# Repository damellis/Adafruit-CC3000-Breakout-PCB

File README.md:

Derivative of the Adafruit CC3000 Breakout PCB
==============================================
This is a derivative of the PCB for the Adafruit CC3000 WiFi Breakout. It adds an ATmega1284 and associated circuitry.

# Original Text Follows

This is the PCB for the Adafruit CC3000 WiFi Breakout
Format is EagleCAD schematic and board layout

For more details, check out the product page at

-----> http://www.adafruit.com/products/1510
-----> http://www.adafruit.com/products/1469

Adafruit invests time and resources providing this open source design, 
please support Adafruit and open-source hardware by purchasing 
products from Adafruit!

Designed by Adafruit Industries.  
Creative Commons Attribution, Share-Alike license, check license.txt for more information
All text above must be included in any redistribution

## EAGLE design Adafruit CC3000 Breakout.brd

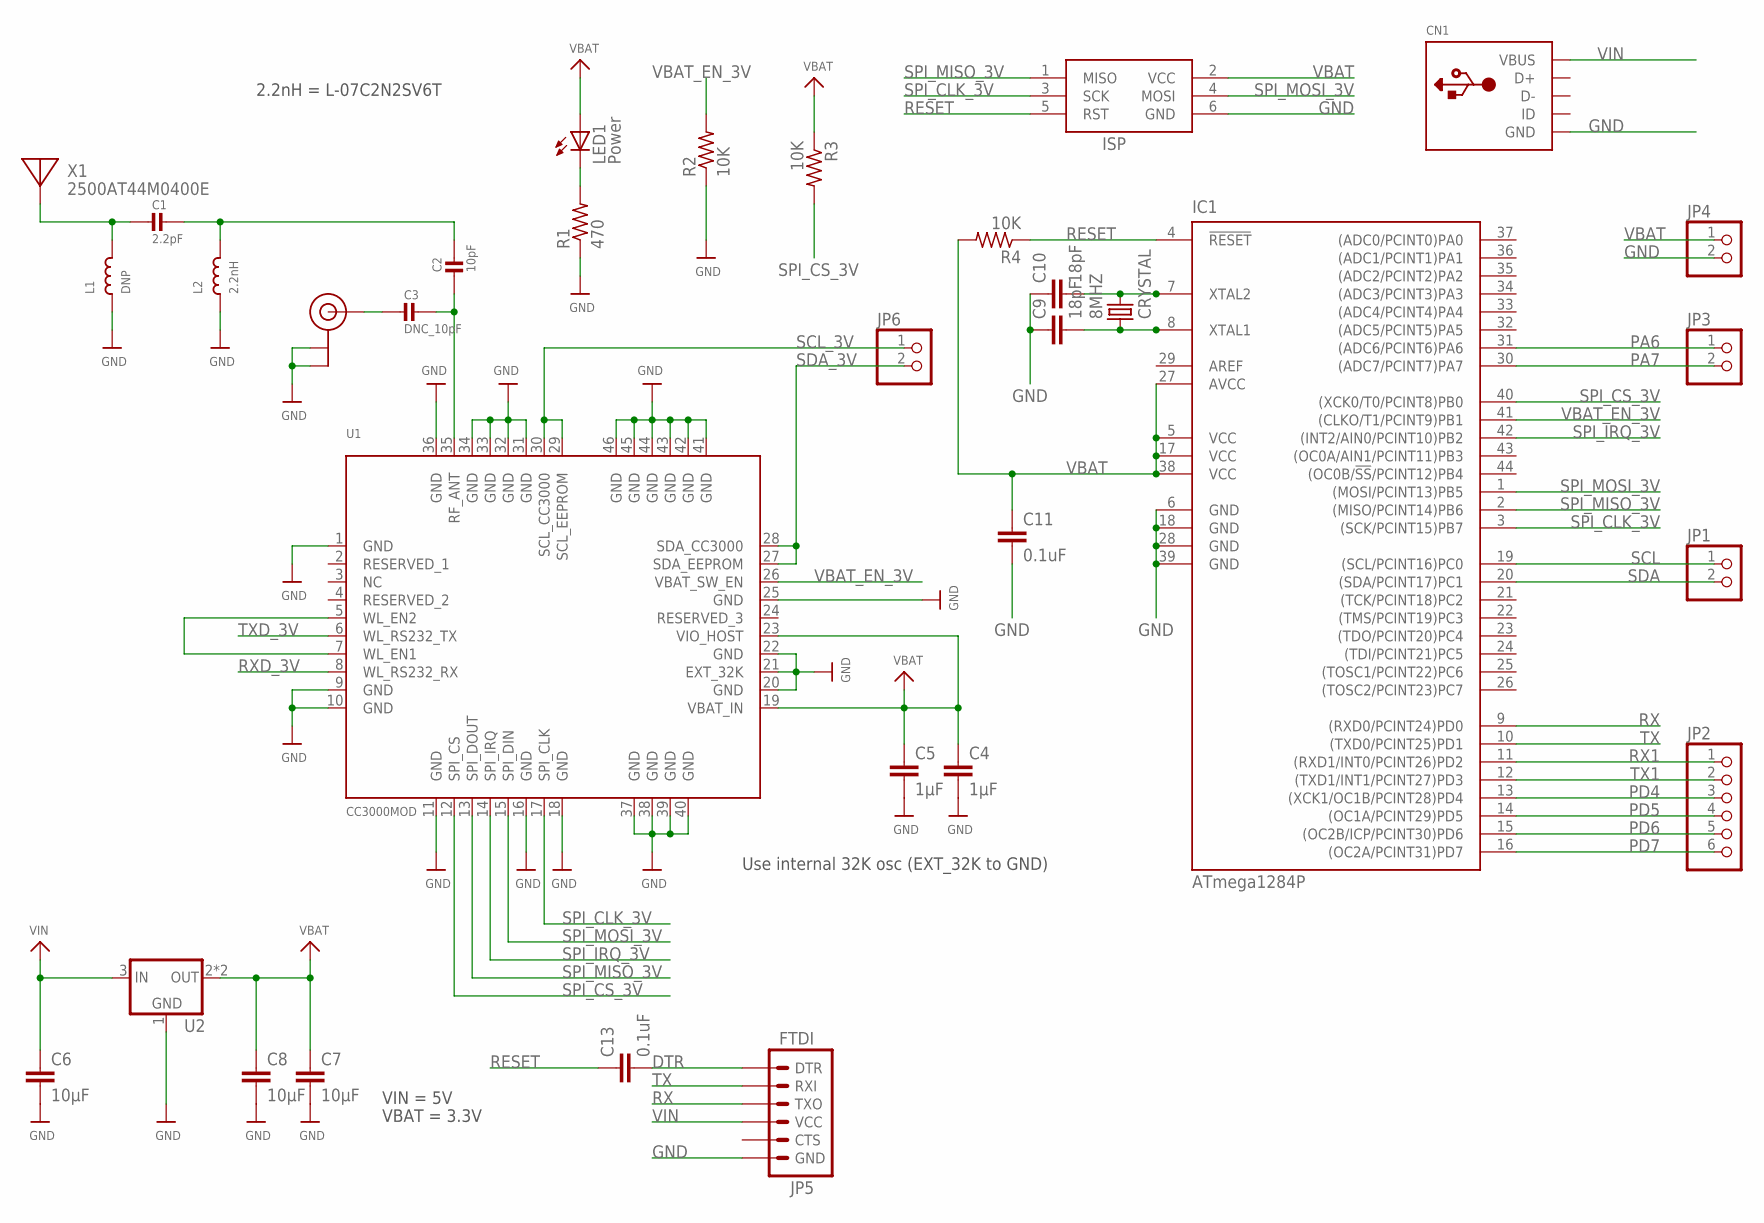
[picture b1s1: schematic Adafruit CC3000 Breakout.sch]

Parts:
8MHZ: CRYSTAL; 2-SMD-5X3MM
C1: 2.2pF; _0402
C2: 10pF; _0402
C3: DNC_10pF; _0402
C4, C5: 1µF; C1206
C6, C7, C8: 10µF; C1206
C9, C10: 18pF; C1206
C11, C13: 0.1uF; C1206
CN1: USBPWR; USB-MINIB-POWER
IC1: ATmega1284P; TQFP44
ISP: AVRISP-6; AVRISP
JP1, JP3, JP4, JP6: PINHD-1X2; 1X02
JP2: PINHD-1X6; 1X06
JP5: FTDI; 1X06
L1: DNP; _0402
L2: 2.2nH; _0402
LED1: Power; 1206
R1: 470; R1206
R2, R3, R4: 10K; R1206
U1: CC3000MOD
U2: VREG_SOT223; SOT223-R
U$35: U.FL
X1: 2500AT44M0400E; ANT_2500AT44M0400

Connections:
AREF: IC1.29 (AREF)
DTR: C13.2, JP5.DTR
GND: C4.2, C5.2, C6.2, C7.2, C8.2, C9.1, C10.1, C11.2, CN1.GND, IC1.6 (GND), IC1.18 (GND), IC1.28 (GND), IC1.39 (GND), ISP.6 (GND), JP4.2, JP5.GND, L1.1, L2.1, R1.1, R2.1, U1.1 (GND), U1.9 (GND), U1.10 (GND), U1.11 (GND), U1.16 (GND), U1.18 (GND), U1.20 (GND), U1.21 (EXT_32K), U1.22 (GND), U1.25 (GND), U1.31 (GND), U1.32 (GND), U1.33 (GND), U1.34 (GND), U1.36 (GND), U1.37 (GND), U1.38 (GND), U1.39 (GND), U1.40 (GND), U1.41 (GND), U1.42 (GND), U1.43 (GND), U1.44 (GND), U1.45 (GND), U1.46 (GND), U2.1 (GND), U$35.P$1 (GND), U$35.P$2 (GND)
unnamed: C1.2, L1.2, X1.FEED
unnamed: C1.1, C2.1, L2.2
unnamed: C3.2, U$35.P$3 (SIGNAL)
unnamed: C2.2, C3.1, U1.35 (RF_ANT)
unnamed: U1.5 (WL_EN2), U1.7 (WL_EN1)
unnamed: LED1.C, R1.2
unnamed: 8MHZ.P$2 (2), C10.2, IC1.7 (XTAL2)
unnamed: 8MHZ.P$1 (1), C9.2, IC1.8 (XTAL1)
PA6: IC1.31 ((ADC6/PCINT6)PA6), JP3.1
PA7: IC1.30 ((ADC7/PCINT7)PA7), JP3.2
PD4: IC1.13 ((XCK1/OC1B/PCINT28)PD4), JP2.3
PD5: IC1.14 ((OC1A/PCINT29)PD5), JP2.4
PD6: IC1.15 ((OC2B/ICP/PCINT30)PD6), JP2.5
PD7: IC1.16 ((OC2A/PCINT31)PD7), JP2.6
RESET: C13.1, IC1.4 (!RESET), ISP.5 (RST), R4.1
RX: IC1.9 ((RXD0/PCINT24)PD0), JP5.TXO
RX1: IC1.11 ((RXD1/INT0/PCINT26)PD2), JP2.1
RXD_3V: U1.8 (WL_RS232_RX)
SCL: IC1.19 ((SCL/PCINT16)PC0), JP1.1
SCL_3V: JP6.1, U1.29 (SCL_EEPROM), U1.30 (SCL_CC3000)
SDA: IC1.20 ((SDA/PCINT17)PC1), JP1.2
SDA_3V: JP6.2, U1.27 (SDA_EEPROM), U1.28 (SDA_CC3000)
SPI_CLK_3V: IC1.3 ((SCK/PCINT15)PB7), ISP.3 (SCK), U1.17 (SPI_CLK)
SPI_CS_3V: IC1.40 ((XCK0/T0/PCINT8)PB0), R3.2, U1.12 (SPI_CS)
SPI_IRQ_3V: IC1.42 ((INT2/AIN0/PCINT10)PB2), U1.14 (SPI_IRQ)
SPI_MISO_3V: IC1.2 ((MISO/PCINT14)PB6), ISP.1 (MISO), U1.13 (SPI_DOUT)
SPI_MOSI_3V: IC1.1 ((MOSI/PCINT13)PB5), ISP.4 (MOSI), U1.15 (SPI_DIN)
TX: IC1.10 ((TXD0/PCINT25)PD1), JP5.RXI
TX1: IC1.12 ((TXD1/INT1/PCINT27)PD3), JP2.2
TXD_3V: U1.6 (WL_RS232_TX)
VBAT: C4.1, C5.1, C7.1, C8.1, C11.1, IC1.5 (VCC), IC1.17 (VCC), IC1.27 (AVCC), IC1.38 (VCC), ISP.2 (VCC), JP4.1, LED1.A, R3.1, R4.2, U1.19 (VBAT_IN), U1.23 (VIO_HOST), U2.2 (OUT), U2.4 (OUT)
VBAT_EN_3V: IC1.41 ((CLKO/T1/PCINT9)PB1), R2.2, U1.26 (VBAT_SW_EN)
VIN: C6.1, CN1.VBUS, JP5.VCC, U2.3 (IN)

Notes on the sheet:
Use internal 32K osc (EXT_32K to GND)
VIN = 5V
VBAT = 3.3V
2.2nH = L-07C2N2SV6T

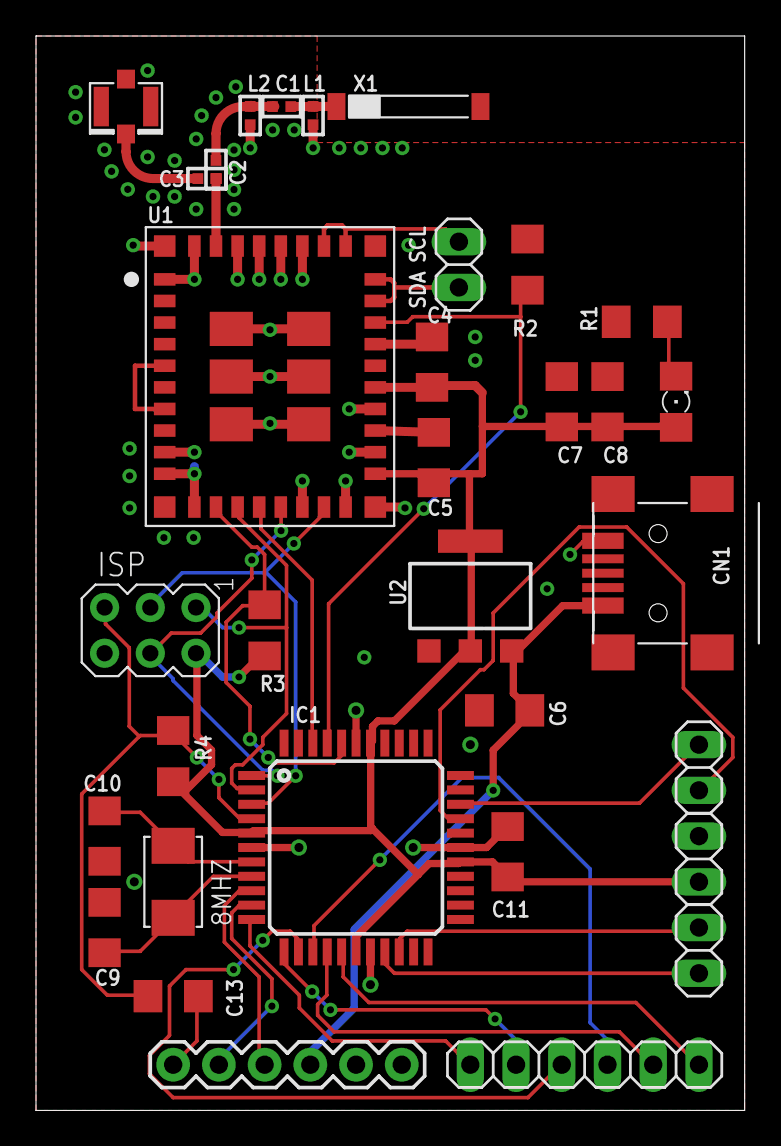
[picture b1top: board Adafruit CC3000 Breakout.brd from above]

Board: 2 copper layers, 39.4 x 59.7 mm, 33 parts (0 on the bottom side), 33 nets.

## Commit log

2015-01-21 Merge with net widget.
    https://github.com/damellis/netwidget
2015-01-21 Smoosh everything together.
    Not routed yet, and some passives are 1206 and others are 0805.
2015-01-21 Remove CC3000 RX and TX debug header.
    And mounting holes.
2015-01-22 Replace passives (w/ 1206), re-layout components.
    Also, change pinouts on the ATmega1284P to match the Wicked Devices
    Wildfire prototyping board. Remove rounded corners.
2015-01-22 Route board.
2015-01-22 Update readme.
2015-01-22 Breakout some microcontroller pins.
    Partly un-route the board.
2015-01-22 Breakout power and ground. Align to inch grid.
2015-01-22 Put CC3000 I2C pins on 0.1" pins.
    Instead of test points.
2015-01-22 Make some ground via's.
    In the hopes it will help with routing.
2015-01-22 Ignore Eagle auto-generated files.
2015-01-22 Add restrict under CC3000 for routing.
2015-01-22 Route.
2015-01-23 Silk screen (and name some traces).
2015-01-23 Tweak a via's position.
2015-01-23 Add date and generate gerbers.

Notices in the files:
parts and their libraries:
microbuilder: This work is placed in the public domain, and may be freely used for commercial and non-commercial work with the following conditions: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
